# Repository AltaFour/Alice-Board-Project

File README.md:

# Alice-Board-Project
Designing a custom Alice layout board for myself

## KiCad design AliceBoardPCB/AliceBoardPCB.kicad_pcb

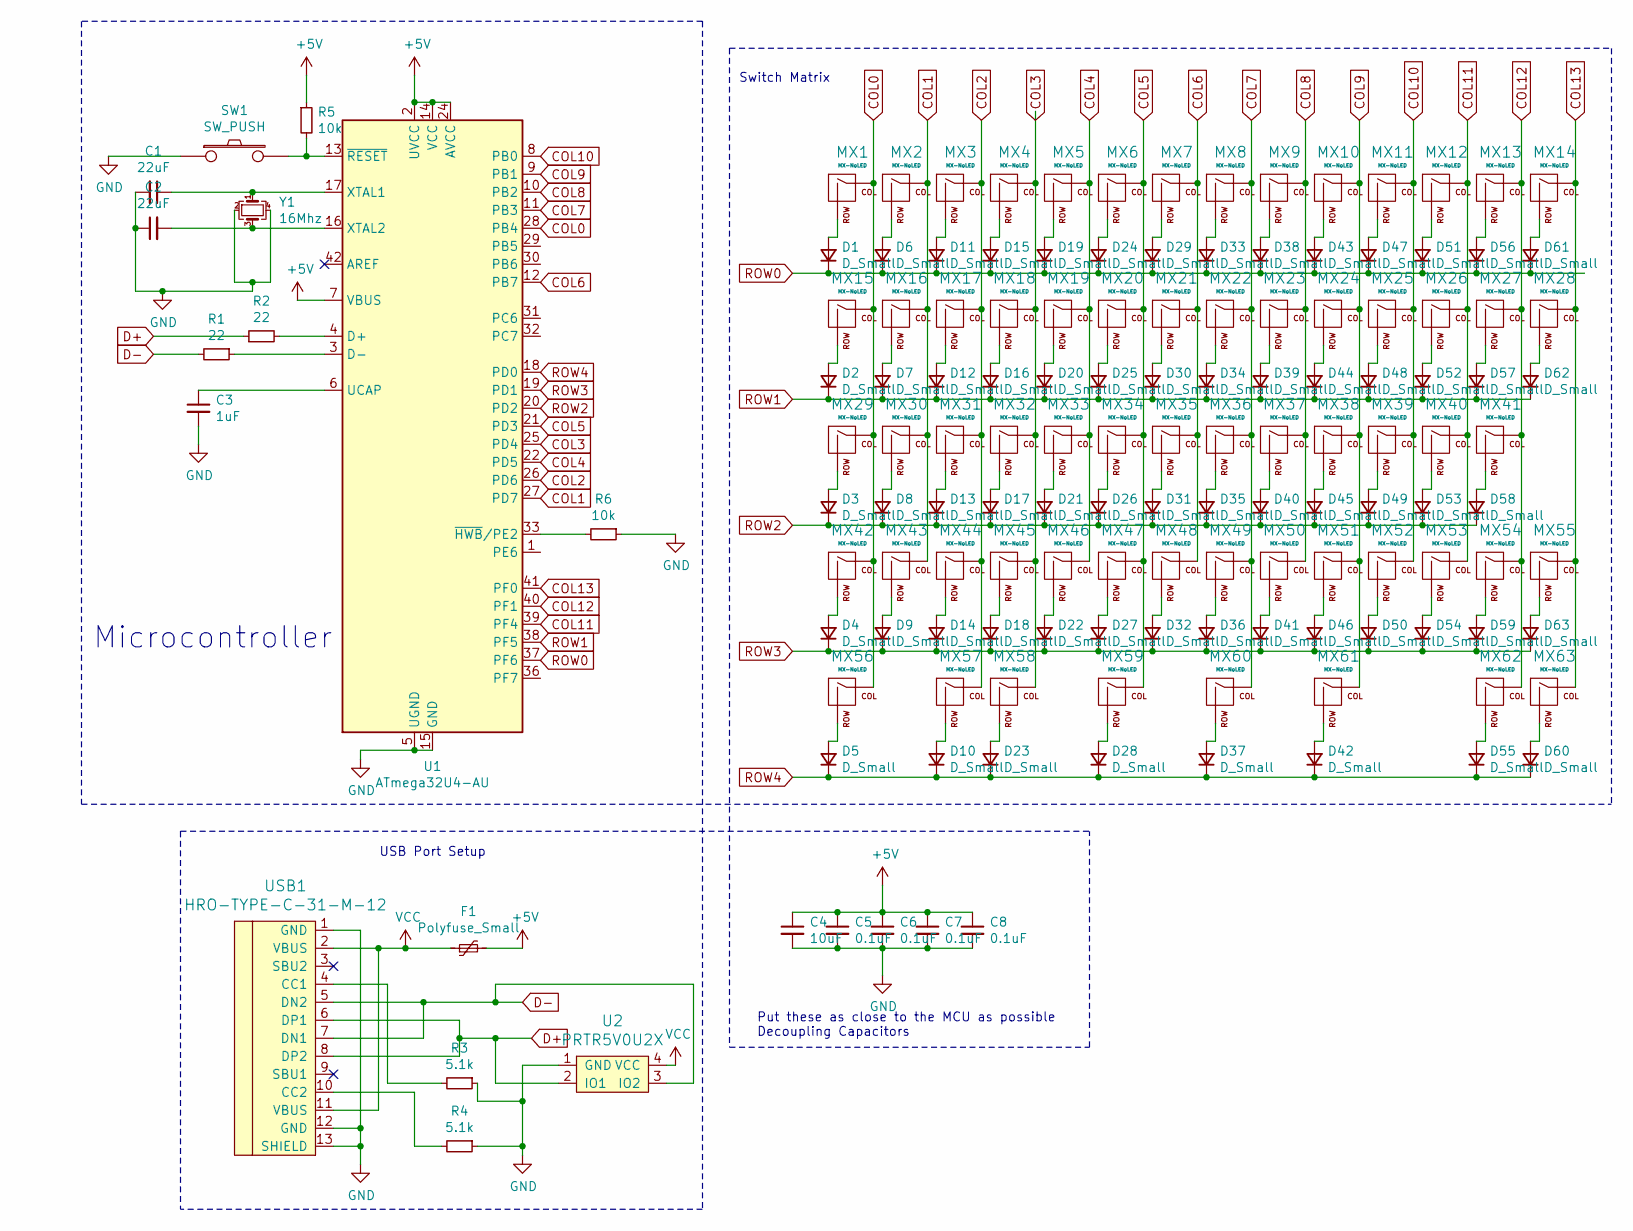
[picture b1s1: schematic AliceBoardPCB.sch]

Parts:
C1, C2: 22uF; C_0805_2012Metric
C3: 1uF; C_0805_2012Metric
C4: 10uF; C_0805_2012Metric
C5, C6, C7, C8: 0.1uF; C_0805_2012Metric
D1, D2, D3, D4, D5, D6, D7, D8, D9, D10, D11, D12, D13, D14, D15, D16, D17, D18, D19, D20, D21, D22, D23, D24, D25, D26, D27, D28, D29, D30, D31, D32, D33, D34, D35, D36, D37, D38, D39, D40, D41, D42, D43, D44, D45, D46, D47, D48, D49, D50, D51, D52, D53, D54, D55, D56, D57, D58, D59, D60, D61, D62, D63: D_Small; D_SOD-123
F1: Polyfuse_Small; Fuse_1206_3216Metric
MX1, MX2, MX3, MX4, MX5, MX6, MX7, MX8, MX9, MX10, MX11, MX12, MX13, MX16, MX17, MX18, MX19, MX20, MX21, MX22, MX23, MX24, MX25, MX26, MX27, MX30, MX31, MX32, MX33, MX34, MX35, MX36, MX37, MX38, MX39, MX40, MX43, MX44, MX45, MX46, MX47, MX48, MX49, MX50, MX51, MX52, MX53, MX55, MX57, MX59: MX-NoLED; MXOnly-1U-NoLED
MX14: MX-NoLED; MXOnly-2U-NoLED
MX15, MX28: MX-NoLED; MXOnly-1.5U-NoLED
MX29, MX54: MX-NoLED; MXOnly-1.75U-NoLED
MX41, MX42, MX58: MX-NoLED; MXOnly-2.25U-NoLED
MX56, MX61, MX62, MX63: MX-NoLED; MXOnly-1.25U-NoLED
MX60: MX-NoLED; MXOnly-2.75U-NoLED
R1, R2: 22; R_0805_2012Metric
R3, R4: 5.1k; R_0805_2012Metric
R5, R6: 10k; R_0805_2012Metric
SW1: SW_PUSH; SKQG-1155865
U1: ATmega32U4-AU; TQFP-44_10x10mm_P0.8mm
U2: PRTR5V0U2X; SOT143B
USB1: HRO-TYPE-C-31-M-12
Y1: 16Mhz; Crystal_SMD_3225-4Pin_3.2x2.5mm

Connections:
+5V: C4.1, C5.1, C6.1, C7.1, C8.1, F1.2, R5.1, U1.2 (UVCC), U1.7 (VBUS), U1.14 (VCC), U1.24 (AVCC), U1.34 (VCC), U1.44 (AVCC)
COL0: MX1.1 (COL), MX15.1 (COL), MX29.1 (COL), MX42.1 (COL), MX56.1 (COL), U1.28 (PB4)
COL1: MX2.1 (COL), MX16.1 (COL), MX30.1 (COL), MX43.1 (COL), U1.27 (PD7)
COL2: MX3.1 (COL), MX17.1 (COL), MX31.1 (COL), MX44.1 (COL), MX57.1 (COL), U1.26 (PD6)
COL3: MX4.1 (COL), MX18.1 (COL), MX32.1 (COL), MX45.1 (COL), MX58.1 (COL), U1.25 (PD4)
COL4: MX5.1 (COL), MX19.1 (COL), MX33.1 (COL), MX46.1 (COL), U1.22 (PD5)
COL5: MX6.1 (COL), MX20.1 (COL), MX34.1 (COL), MX47.1 (COL), MX59.1 (COL), U1.21 (PD3)
COL6: MX7.1 (COL), MX21.1 (COL), MX35.1 (COL), MX48.1 (COL), U1.12 (PB7)
COL7: MX8.1 (COL), MX22.1 (COL), MX36.1 (COL), MX49.1 (COL), MX60.1 (COL), U1.11 (PB3)
COL8: MX9.1 (COL), MX23.1 (COL), MX37.1 (COL), MX50.1 (COL), U1.10 (PB2)
COL9: MX10.1 (COL), MX24.1 (COL), MX38.1 (COL), MX51.1 (COL), MX61.1 (COL), U1.9 (PB1)
COL10: MX11.1 (COL), MX25.1 (COL), MX39.1 (COL), MX52.1 (COL), U1.8 (PB0)
COL11: MX12.1 (COL), MX26.1 (COL), MX40.1 (COL), MX53.1 (COL), U1.39 (PF4)
COL12: MX13.1 (COL), MX27.1 (COL), MX41.1 (COL), MX54.1 (COL), MX62.1 (COL), U1.40 (PF1)
COL13: MX14.1 (COL), MX28.1 (COL), MX55.1 (COL), MX63.1 (COL), U1.41 (PF0)
D+: R2.1, U2.2 (IO1), USB1.6 (DP1), USB1.8 (DP2)
D-: R1.2, U2.3 (IO2), USB1.5 (DN2), USB1.7 (DN1)
GND: C1.2, C2.1, C3.2, C4.2, C5.2, C6.2, C7.2, C8.2, R3.1, R4.1, R6.1, SW1.1, U1.5 (UGND), U1.15 (GND), U1.23 (GND), U1.35 (GND), U1.43 (GND), U2.1 (GND), USB1.1 (GND), USB1.12 (GND), USB1.13 (SHIELD), Y1.2, Y1.4
unnamed: C1.1, U1.17 (XTAL1), Y1.1
unnamed: C2.2, U1.16 (XTAL2), Y1.3
unnamed: C3.1, U1.6 (UCAP)
unnamed: D1.2 (A), MX1.2 (ROW)
unnamed: D2.2 (A), MX15.2 (ROW)
unnamed: D3.2 (A), MX29.2 (ROW)
unnamed: D4.2 (A), MX42.2 (ROW)
unnamed: D5.2 (A), MX56.2 (ROW)
unnamed: D6.2 (A), MX2.2 (ROW)
unnamed: D7.2 (A), MX16.2 (ROW)
unnamed: D8.2 (A), MX30.2 (ROW)
unnamed: D9.2 (A), MX43.2 (ROW)
unnamed: D10.2 (A), MX57.2 (ROW)
unnamed: D11.2 (A), MX3.2 (ROW)
unnamed: D12.2 (A), MX17.2 (ROW)
unnamed: D13.2 (A), MX31.2 (ROW)
unnamed: D14.2 (A), MX44.2 (ROW)
unnamed: D15.2 (A), MX4.2 (ROW)
unnamed: D16.2 (A), MX18.2 (ROW)
unnamed: D17.2 (A), MX32.2 (ROW)
unnamed: D18.2 (A), MX45.2 (ROW)
unnamed: D19.2 (A), MX5.2 (ROW)
unnamed: D20.2 (A), MX19.2 (ROW)
unnamed: D21.2 (A), MX33.2 (ROW)
unnamed: D22.2 (A), MX46.2 (ROW)
unnamed: D23.2 (A), MX58.2 (ROW)
unnamed: D24.2 (A), MX6.2 (ROW)
unnamed: D25.2 (A), MX20.2 (ROW)
unnamed: D26.2 (A), MX34.2 (ROW)
unnamed: D27.2 (A), MX47.2 (ROW)
unnamed: D28.2 (A), MX59.2 (ROW)
unnamed: D29.2 (A), MX7.2 (ROW)
unnamed: D30.2 (A), MX21.2 (ROW)
unnamed: D31.2 (A), MX35.2 (ROW)
unnamed: D32.2 (A), MX48.2 (ROW)
unnamed: D33.2 (A), MX8.2 (ROW)
unnamed: D34.2 (A), MX22.2 (ROW)
unnamed: D35.2 (A), MX36.2 (ROW)
unnamed: D36.2 (A), MX49.2 (ROW)
unnamed: D37.2 (A), MX60.2 (ROW)
unnamed: D38.2 (A), MX9.2 (ROW)
unnamed: D39.2 (A), MX23.2 (ROW)
unnamed: D40.2 (A), MX37.2 (ROW)
unnamed: D41.2 (A), MX50.2 (ROW)
unnamed: D42.2 (A), MX61.2 (ROW)
unnamed: D43.2 (A), MX10.2 (ROW)
unnamed: D44.2 (A), MX24.2 (ROW)
unnamed: D45.2 (A), MX38.2 (ROW)
unnamed: D46.2 (A), MX51.2 (ROW)
unnamed: D47.2 (A), MX11.2 (ROW)
unnamed: D48.2 (A), MX25.2 (ROW)
unnamed: D49.2 (A), MX39.2 (ROW)
unnamed: D50.2 (A), MX52.2 (ROW)
unnamed: D51.2 (A), MX12.2 (ROW)
unnamed: D52.2 (A), MX26.2 (ROW)
unnamed: D53.2 (A), MX40.2 (ROW)
unnamed: D54.2 (A), MX53.2 (ROW)
unnamed: D55.2 (A), MX62.2 (ROW)
unnamed: D56.2 (A), MX13.2 (ROW)
unnamed: D57.2 (A), MX27.2 (ROW)
unnamed: D58.2 (A), MX41.2 (ROW)
unnamed: D59.2 (A), MX54.2 (ROW)
unnamed: D60.2 (A), MX63.2 (ROW)
unnamed: D61.2 (A), MX14.2 (ROW)
unnamed: D62.2 (A), MX28.2 (ROW)
unnamed: D63.2 (A), MX55.2 (ROW)
unnamed: R1.1, U1.3 (D-)
unnamed: R2.2, U1.4 (D+)
unnamed: R3.2, USB1.4 (CC1)
unnamed: R4.2, USB1.10 (CC2)
unnamed: R5.2, SW1.2, U1.13 (~RESET)
unnamed: R6.2, U1.33 (~HWB~/PE2)
ROW0: D1.1 (K), D6.1 (K), D11.1 (K), D15.1 (K), D19.1 (K), D24.1 (K), D29.1 (K), D33.1 (K), D38.1 (K), D43.1 (K), D47.1 (K), D51.1 (K), D56.1 (K), D61.1 (K), U1.37 (PF6)
ROW1: D2.1 (K), D7.1 (K), D12.1 (K), D16.1 (K), D20.1 (K), D25.1 (K), D30.1 (K), D34.1 (K), D39.1 (K), D44.1 (K), D48.1 (K), D52.1 (K), D57.1 (K), D62.1 (K), U1.38 (PF5)
ROW2: D3.1 (K), D8.1 (K), D13.1 (K), D17.1 (K), D21.1 (K), D26.1 (K), D31.1 (K), D35.1 (K), D40.1 (K), D45.1 (K), D49.1 (K), D53.1 (K), D58.1 (K), U1.20 (PD2)
ROW3: D4.1 (K), D9.1 (K), D14.1 (K), D18.1 (K), D22.1 (K), D27.1 (K), D32.1 (K), D36.1 (K), D41.1 (K), D46.1 (K), D50.1 (K), D54.1 (K), D59.1 (K), D63.1 (K), U1.19 (PD1)
ROW4: D5.1 (K), D10.1 (K), D23.1 (K), D28.1 (K), D37.1 (K), D42.1 (K), D55.1 (K), D60.1 (K), U1.18 (PD0)
VCC: F1.1, U2.4 (VCC), USB1.2 (VBUS), USB1.11 (VBUS)

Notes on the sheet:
Put these as close to the MCU as possible Decoupling Capacitors
Switch Matrix
USB Port Setup
Microcontroller

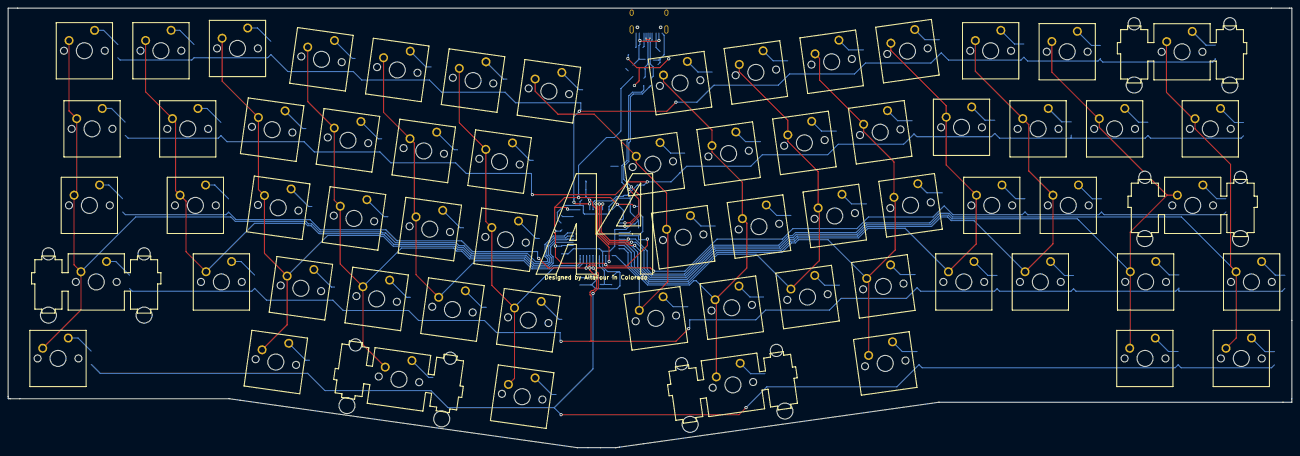
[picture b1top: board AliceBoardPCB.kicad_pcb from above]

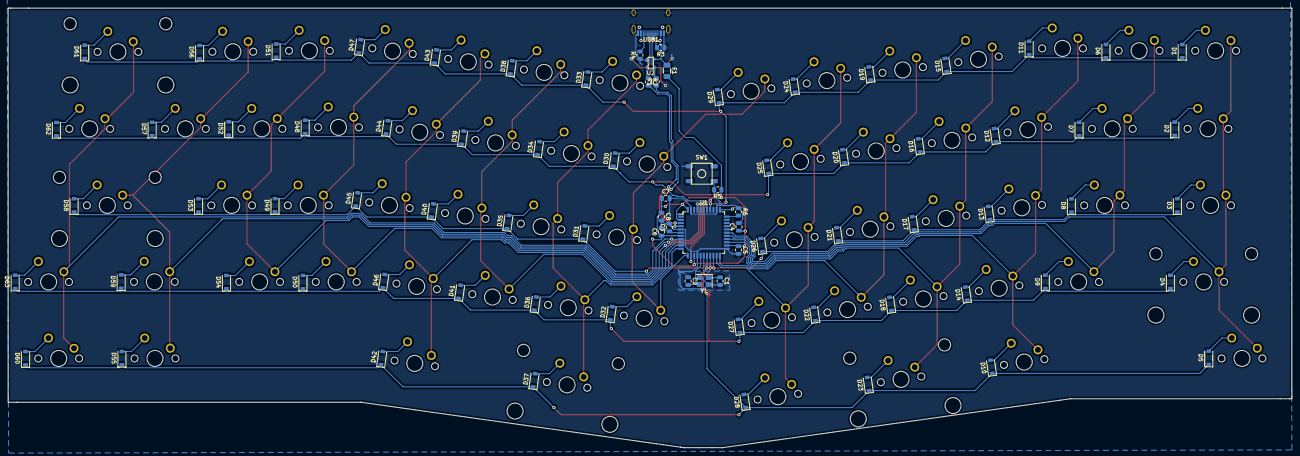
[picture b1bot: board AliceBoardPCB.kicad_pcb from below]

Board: 2 copper layers, 319.5 x 109.4 mm, 146 parts (83 on the bottom side), 96 nets.

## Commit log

2021-04-12 Inventor Switch
    I switched my design over to inventor and it is now a saveable file that i can commit to GitHub
2021-04-24 Add Submodules(Libraries)
2021-04-24 GitHub Desktop Sucks
    why r u like this
2021-04-24 Add Submodules
2021-04-24 Adding Submodules
2021-04-24 FirstStart
    First start on PCB
2021-04-29 Big Submodule Library
2021-04-29 Daughterboard Submodule
2021-04-30 Schematic and Acrylic Case
    Finished the pcb schematic and im starting the acrylic case.
2021-05-11 Switch Matrix PCB Layour
    Finished up the PCB layout for the switch matrix. I just have to do the wire routing and placement of the processing components. Its going well!
2021-05-12 PCB Update
    more pcb updates
2021-05-13 First Draft!
    I finished my first draft for the PCB. Im gonna work on making it look better and stuff but other than that its most likely functional and yea! Super excited to where this is going.
2021-05-13 Finished PCB
    Less Gooooo
2023-08-09 PhotoForReadMe
